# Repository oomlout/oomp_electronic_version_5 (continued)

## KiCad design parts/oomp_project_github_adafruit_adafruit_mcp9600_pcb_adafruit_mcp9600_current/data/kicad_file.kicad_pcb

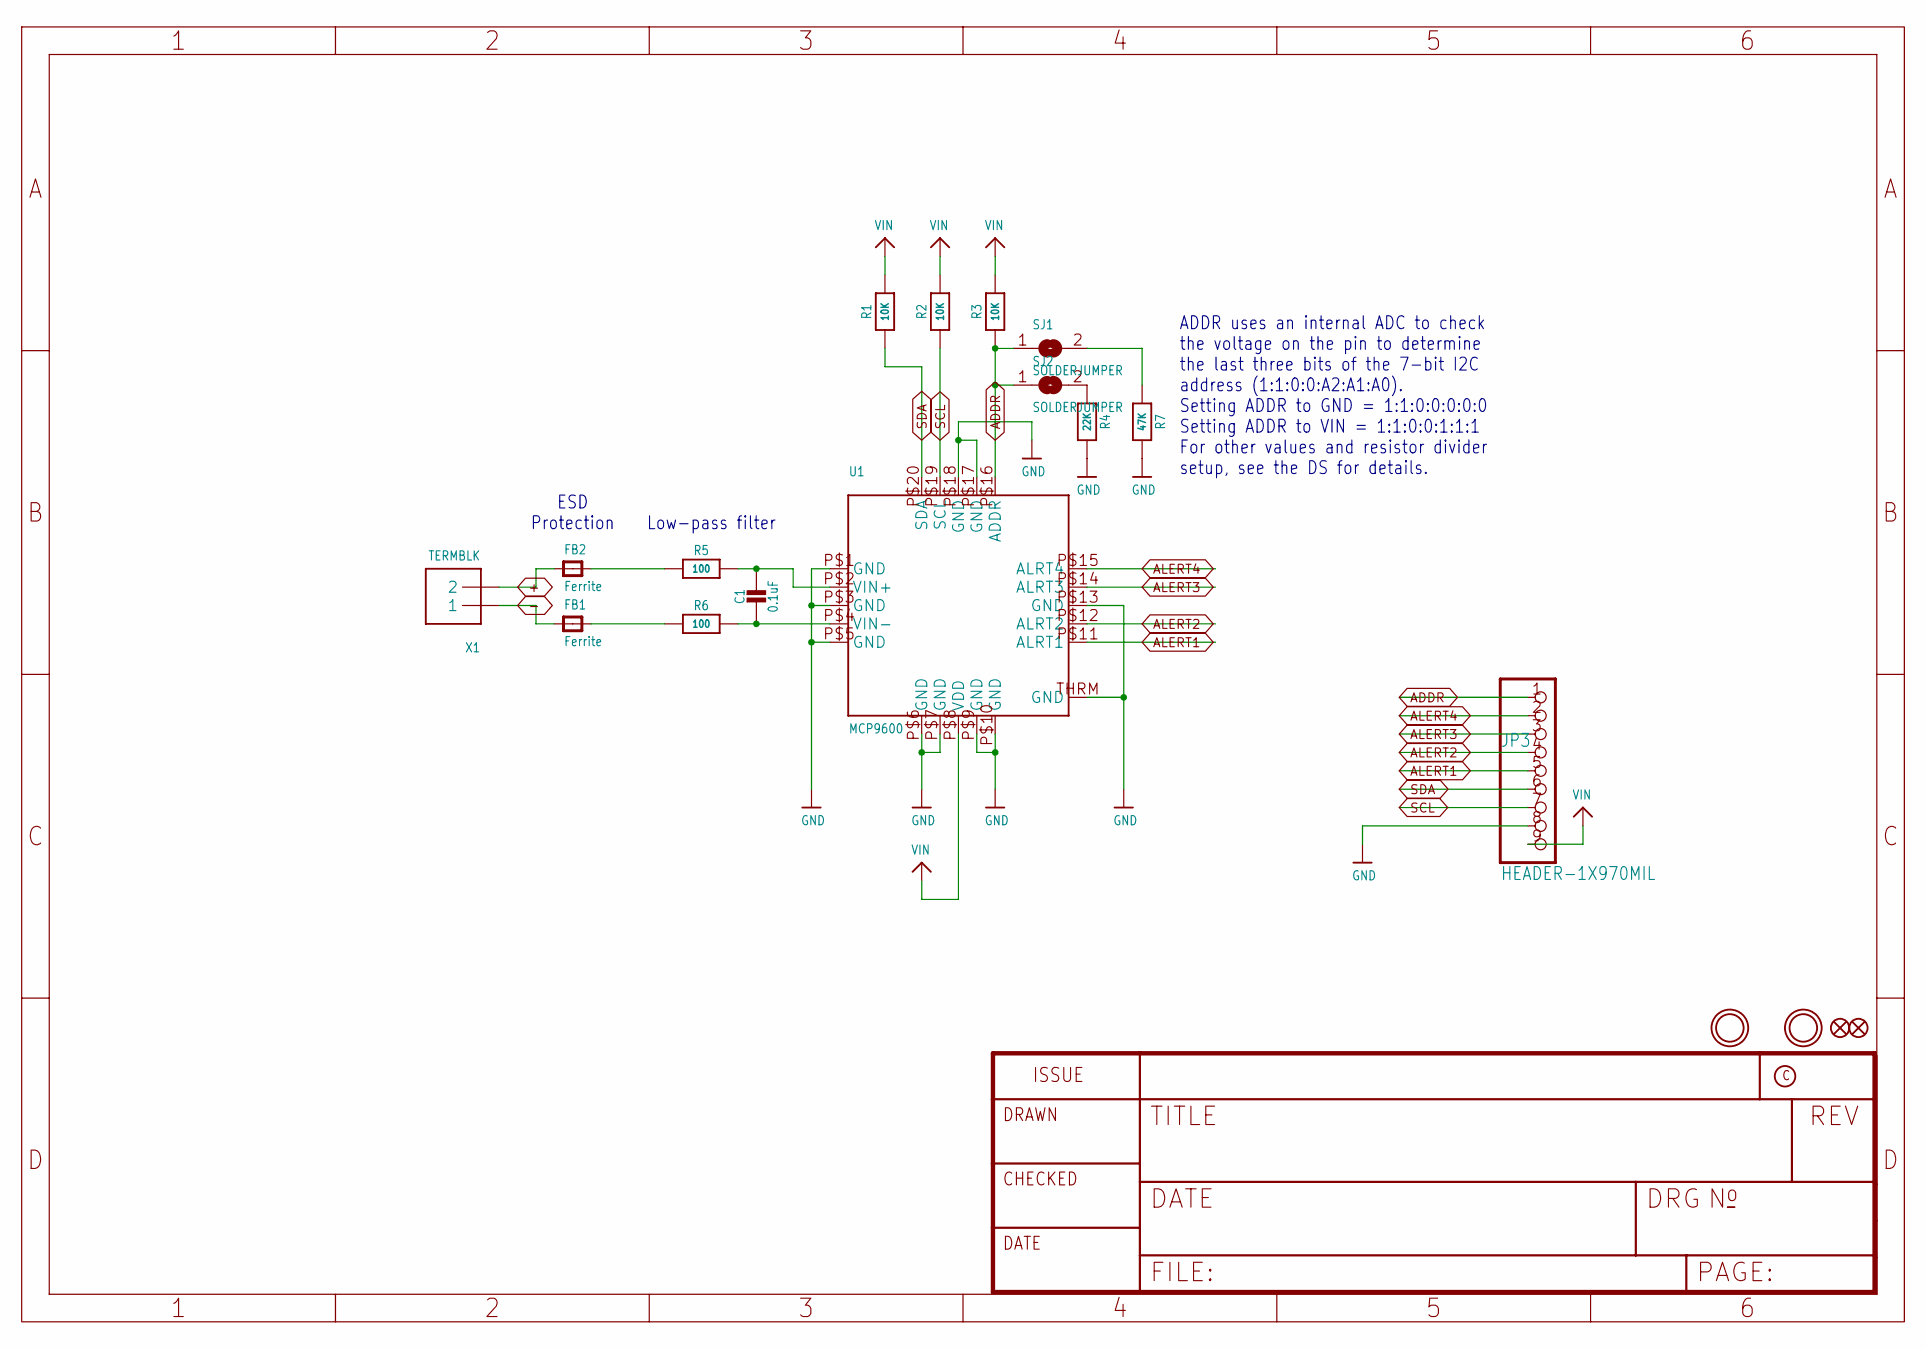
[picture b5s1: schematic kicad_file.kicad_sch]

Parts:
C1: 0.1uF; 0603-NO
FB1, FB2: Ferrite; 0805-NO
FID1, FID2: FIDUCIAL_1MM
JP3: HEADER-1X970MIL; 1X09_ROUND_70
R1, R2, R3: 10K; 0603-NO
R4: 22K; 0603-NO
R5, R6: 100; 0603-NO
R7: 47K; 0603-NO
SJ1, SJ2: SOLDERJUMPER; SOLDERJUMPER_ARROW_NOPASTE
U1: MCP9600; VQFN20_5MM
U$1, U$3: MOUNTINGHOLE2.5; MOUNTINGHOLE_2.5_PLATED
X1: TERMBLK; TERMBLOCK_1X2-3.5MM

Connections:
+: FB2.1, X1.2
-: FB1.1, X1.1
ADDR: JP3.1, R3.1, SJ1.1, SJ2.1, U1.P$16 (ADDR)
ALERT1: JP3.5, U1.P$11 (ALRT1)
ALERT2: JP3.4, U1.P$12 (ALRT2)
ALERT3: JP3.3, U1.P$14 (ALRT3)
ALERT4: JP3.2, U1.P$15 (ALRT4)
GND: JP3.8, R4.2, R7.2, U1.P$1 (GND), U1.P$3 (GND), U1.P$5 (GND), U1.P$6 (GND), U1.P$7 (GND), U1.P$9 (GND), U1.P$10 (GND), U1.P$13 (GND), U1.P$17 (GND), U1.P$18 (GND), U1.THRM (GND)
unnamed: C1.1, R5.2, U1.P$2 (VIN+)
unnamed: C1.2, R6.2, U1.P$4 (VIN-)
unnamed: FB1.2, R6.1
unnamed: FB2.2, R5.1
unnamed: R7.1, SJ1.2
unnamed: R4.1, SJ2.2
SCL: JP3.7, R2.1, U1.P$19 (SCL)
SDA: JP3.6, R1.1, U1.P$20 (SDA)
VIN: JP3.9, R1.2, R2.2, R3.2, U1.P$8 (VDD)

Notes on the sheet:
ESD Protection
ADDR uses an internal ADC to check the voltage on the pin to determine the last three bits of the 7-bit I2C address (1:1:0:0:A2:A1:A0). Setting ADDR to GND = 1:1:0:0:0:0:0 Setting ADDR to VIN = 1:1:0:0:1:1:1 For other values and resistor divider setup, see the DS for details.
Low-pass filter

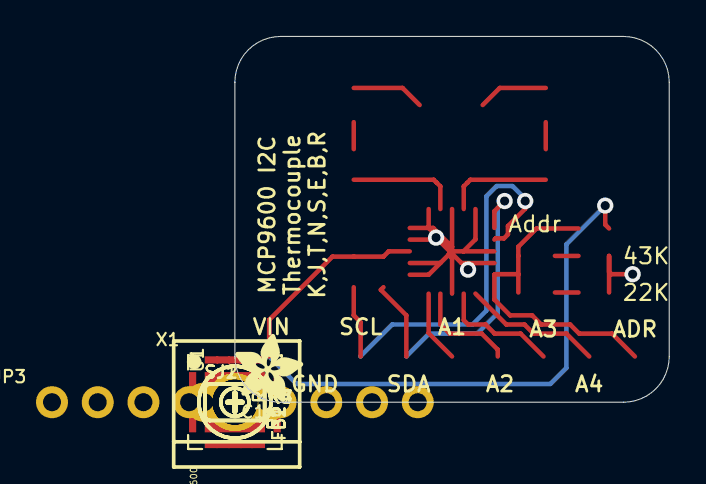
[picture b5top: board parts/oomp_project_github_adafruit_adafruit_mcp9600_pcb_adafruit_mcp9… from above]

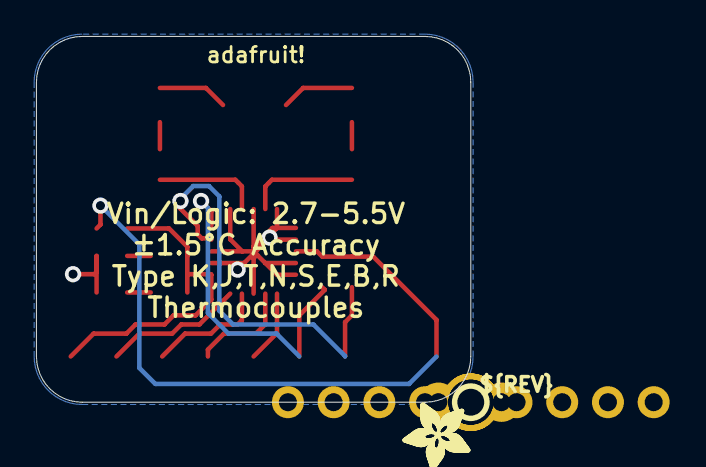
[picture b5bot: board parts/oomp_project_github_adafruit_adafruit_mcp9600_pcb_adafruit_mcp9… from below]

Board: 2 copper layers, 24.1 x 20.3 mm, 25 parts (3 on the bottom side), 17 nets.

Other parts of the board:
U$16, U$19, U$20: ADAFRUIT_3.5MM
U$17: SYMBOL_PLUS
U$18: SYMBOL_MINUS
U$21: PCBFEAT-REV-040

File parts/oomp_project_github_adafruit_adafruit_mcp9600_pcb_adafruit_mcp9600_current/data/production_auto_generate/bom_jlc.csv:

Comment,Designator,Footprint,LCSC Part #
,JP3,Adafruit MCP9600-import-fps:1X09_ROUND_70,C2932701
,"U$16,U$19,U$20",Adafruit MCP9600-import-fps:ADAFRUIT_3.5MM,
,U$21,Adafruit MCP9600-import-fps:PCBFEAT-REV-040,
,U$18,Adafruit MCP9600-import-fps:SYMBOL_MINUS,
,U$17,Adafruit MCP9600-import-fps:SYMBOL_PLUS,
0.1uF,C1,Adafruit MCP9600-import-fps:0603-NO,C14663
100,"R5,R6",Adafruit MCP9600-import-fps:0603-NO,C22775
10K,"R1,R2,R3",Adafruit MCP9600-import-fps:0603-NO,C98220
22K,R4,Adafruit MCP9600-import-fps:0603-NO,C31850
47K,R7,Adafruit MCP9600-import-fps:0603-NO,C2907042
Ferrite,"FB1,FB2",Adafruit MCP9600-import-fps:0805-NO,
MCP9600,U1,Adafruit MCP9600-import-fps:VQFN20_5MM,
TERMBLK,X1,Adafruit MCP9600-import-fps:TERMBLOCK_1X2-3.5MM,
